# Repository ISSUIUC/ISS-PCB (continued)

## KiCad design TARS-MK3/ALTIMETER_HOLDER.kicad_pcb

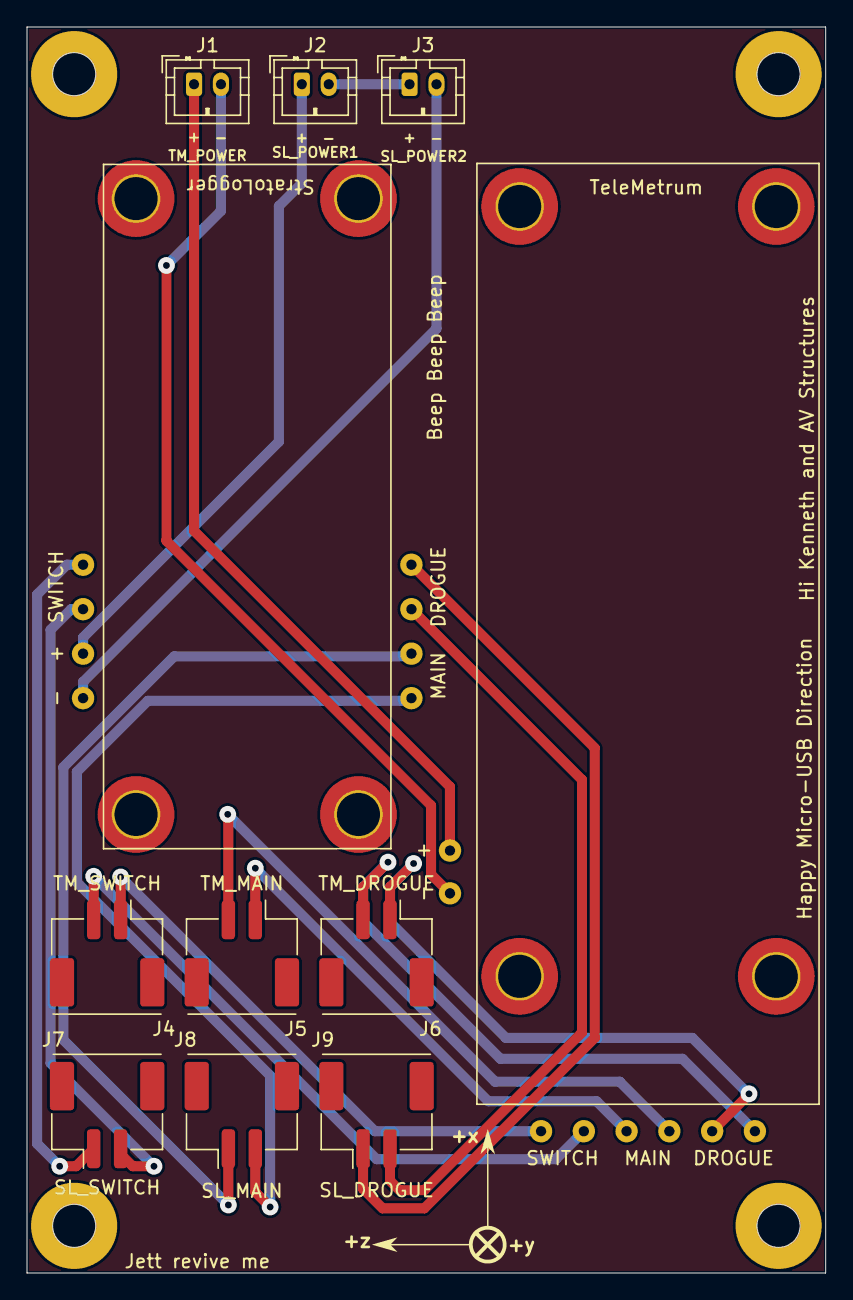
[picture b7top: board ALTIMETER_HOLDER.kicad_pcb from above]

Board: 2 copper layers, 59.3 x 92.5 mm, 11 parts (0 on the bottom side), 17 nets.

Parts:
A1: TeleMetrum
A2: StratoLogger
J1, J2, J3: Conn_01x02_Female; JST_PH_B2B-PH-K_1x02_P2.00mm_Vertical
J4, J5, J6, J7, J8, J9: Conn_01x02_Female; Molex_CLIK-Mate_502443-0270_1x02-1MP_P2.00mm_Vertical

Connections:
/SL_DROGUE_N: A2.6 (DROGUE1), J9.2
/SL_DROGUE_P: A2.5 (DROGUE0), J9.1
/SL_MAIN_N: A2.8 (MAIN1), J8.2
/SL_MAIN_P: A2.7 (MAIN0), J8.1
/SL_SWITCH_N: A2.2 (SWITCH1), J7.2
/SL_SWITCH_P: A2.1 (SWITCH0), J7.1
/TM_DROGUE_N: A1.8 (DROGUE1), J6.2
/TM_DROGUE_P: A1.7 (DROGUE0), J6.1
/TM_MAIN_N: A1.6 (MAIN1), J5.2
/TM_MAIN_P: A1.5 (MAIN0), J5.1
/TM_SWITCH_N: A1.4 (SWITCH1), J4.2
/TM_SWITCH_P: A1.3 (SWITCH0), J4.1
unnamed: J2.2, J3.1
SL_POWER_NEGATIVE: A2.4 (NEGATIVE), J3.2
SL_POWER_POSITIVE: A2.3 (POSITIVE), J2.1
TM_POWER_NEGATIVE: A1.2 (NEGATIVE), J1.2
TM_POWER_POSITIVE: A1.1 (POSITIVE), J1.1
